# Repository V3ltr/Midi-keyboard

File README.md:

[BOM.csv](https://github.com/user-attachments/files/33931853/BOM.csv)

This is a Midi keyboard. 
It uses touch sensors that sense your electromagnetical field and activate sending a signal to the waveshare ESP32 S3 Zero.
It works like a electric keyboard, with switches, buttons, knobs, and sliders that control the sound.
The sound is output from your phone thanks to the waveshare esp. 

Part,What it's for,Qty,Unit $,Vendor,Link
Waveshare esp32 S3 Zero,Micro-controller,1,12.36,pajenicko,https://pajenicko.cz/waveshare-esp32-s3-zero-vyvojova-deska
MX1 cherry switches,The button,1,6,CTRLshop,https://www.ctrlshop.cz/products/cherry-mx-purple-switch
TTP223,sensing a touch,1,1.15,Dratek,https://dratek.cz/arduino-platforma/1402-ttp223-kapacitni-dotykovy-spinac-tlacitko-self-lock-modul-pro-arduino.html
Potentiometer 10K,Sliders for Bass+Pitch,2,4.88,dratek,https://dratek.cz/arduino-platforma/1291-10k-tahovy-linearni-potenciometr-pro-arduino.html
Rotary encoder,For setting the volume,1,1.33,dratek,https://dratek.cz/arduino-platforma/837-rotacni-enkoder.html

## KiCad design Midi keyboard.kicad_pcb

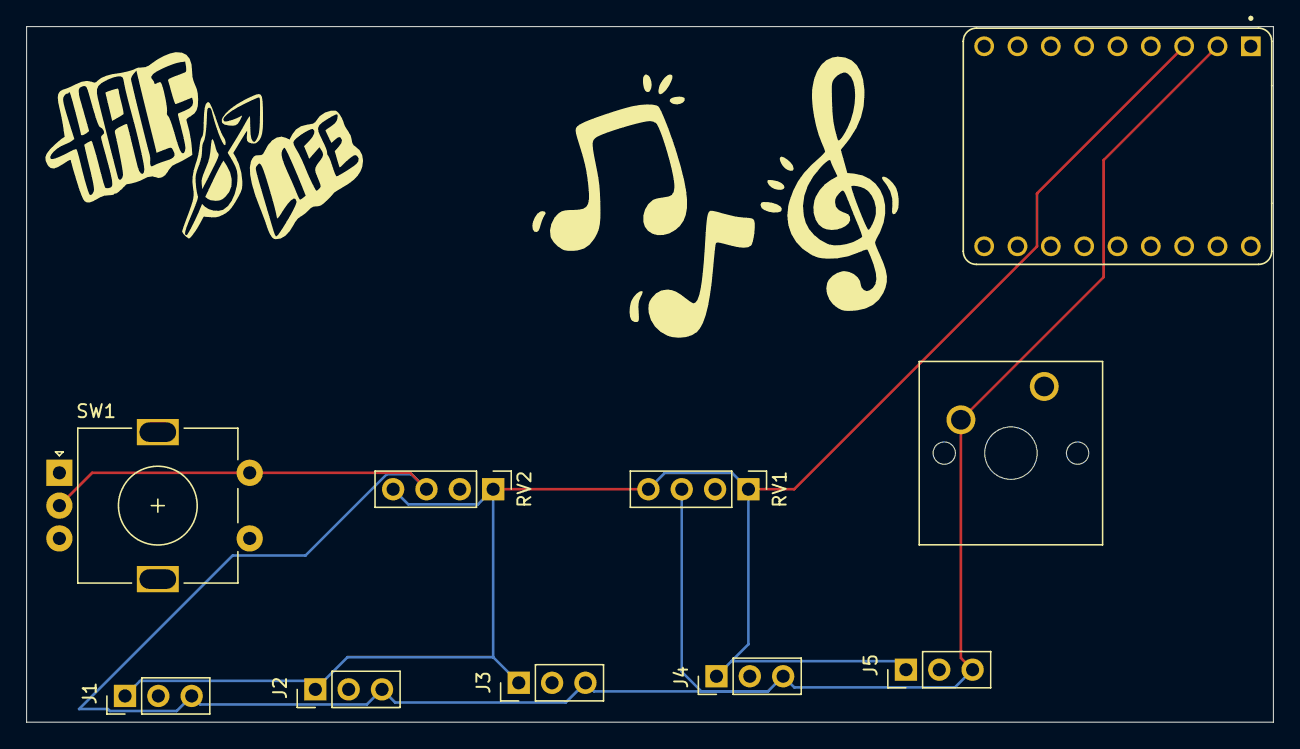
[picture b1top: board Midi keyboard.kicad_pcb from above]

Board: 2 copper layers, 95.0 x 53.0 mm, 10 parts (0 on the bottom side), 2 nets.

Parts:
J1, J2, J3, J4, J5: Conn_01x03_Pin; PinHeader_1x03_P2.54mm_Vertical
RV1, RV2: R_Potentiometer_Dual; PinHeader_1x04_P2.54mm_Vertical
SW1: RotaryEncoder_Switch; RotaryEncoder_Alps_EC11E-Switch_Vertical_H20mm
SW2: SW_Push; SW_Cherry_MX_1.00u_PCB
U1: Waveshare ESP32-S3-ZERO; Waveshare ESP32-S3-Zero

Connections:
+3V3: J1.1, J2.1, J3.1, J4.1, J5.1, RV1.1, RV1.4, RV2.1, RV2.4, U1.3V3 (3V3(OUT))
GND: J1.3, J2.3, J3.3, J4.3, J5.3, RV1.3, RV2.3, SW1.C, SW1.S2, SW2.2, U1.GND
